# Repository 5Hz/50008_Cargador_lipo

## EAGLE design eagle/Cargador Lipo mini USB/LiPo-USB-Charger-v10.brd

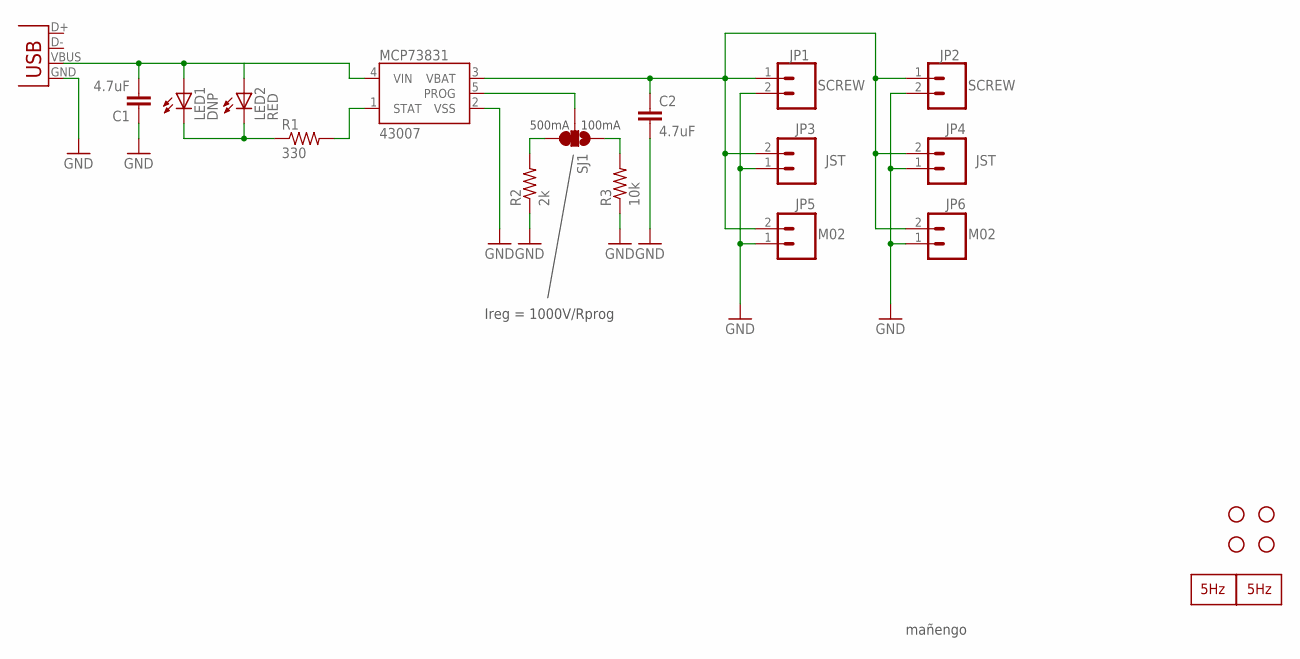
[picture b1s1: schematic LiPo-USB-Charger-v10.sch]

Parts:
C1, C2: 4.7uF; 0402-CAP
JP1, JP2: SCREW; SCREWTERMINAL-3.5MM-2-NS
JP3, JP4: JST; JST-2-PTH
JP5, JP6: M02; 1X02
JP7, JP8, JP9, JP10: STAND-OFF
LED1: DNP; LED3MM
LED2: RED; LED-0603
MCP73831: 43007; SOT23-5
R1: 330; 0402-RES
R2: 2k; 0402-RES
R3: 10k; 0402-RES
SJ1: SOLDERJUMPER_2WAYS; SJ_3
U$1: LOGO_COPPER10MM; LOGO_COP_10MM
U$2: LOGO2_SILK5MM; LOGO2_5MM
X1: USBSMD; USB-MINIB

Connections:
GND: C1.1, C2.2, JP1.2, JP2.2, JP3.1, JP4.1, JP5.1, JP6.1, MCP73831.2 (VSS), R2.1, R3.1, X1.GND
unnamed: C1.2, LED1.A, LED2.A, MCP73831.4 (VIN), X1.VBUS
unnamed: MCP73831.1 (STAT), R1.2
unnamed: LED1.K (C), LED2.C, R1.1
unnamed: R2.2, SJ1.3
unnamed: R3.2, SJ1.1
PROG: MCP73831.5 (PROG), SJ1.2
VBAT: C2.1, JP1.1, JP2.1, JP3.2, JP4.2, JP5.2, JP6.2, MCP73831.3 (VBAT)

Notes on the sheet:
500mA
100mA
Ireg = 1000V/Rprog
mañengo

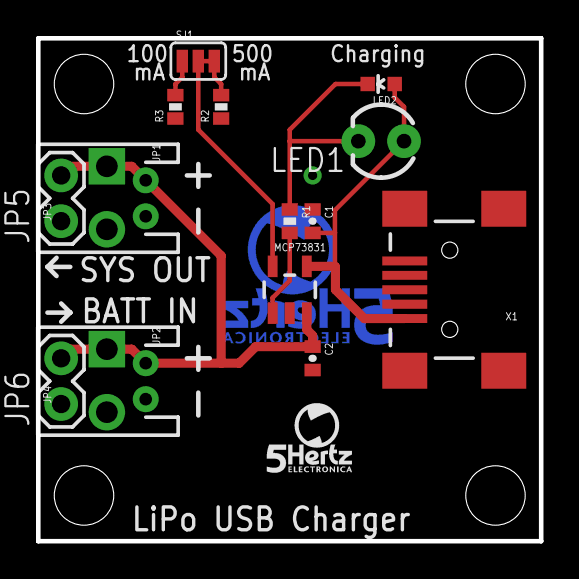
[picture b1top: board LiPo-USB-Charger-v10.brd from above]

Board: 2 copper layers, 27.9 x 27.9 mm, 22 parts (1 on the bottom side), 8 nets.

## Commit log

2014-01-09 creación
